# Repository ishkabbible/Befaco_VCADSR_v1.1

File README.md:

# Befaco_VCADSR_v1.1
Hamara Labs modified version of the Befaco version 1 VCADSR

The original files from Befaco are available here:
https://www.befaco.org/en/sinte-modular/en-produccion/vc-adsrv1/

Original design by Juergen Haible (http://www.jhaible.info/tonline_stuff/hj_vc_hadsr.html)

and Tom Gamble (http://synthdiy.fonitronik.de/files/4613/8287/9784/vcradsr.pdf)

I fixed a couple of bugs
  1) the inputs to the unused half of the 4013 were left floating - they are now properly grounded
  2) The trigger input to the used half of the 4013 was effectively floating whenever there was no gate input present, 
  due to the reverse biased D2. Added R26 to hold the trigger input at ground when D2 is reverse biased
  3) A retrigger bug was identified by someone somewhere, and photos of a haywire patch have been routinely distributed on line.
  That mod has been incorporated on the PCB as D6 and T8
  
I also updated the layout to use parts that are more readily available than the parts used in the original design. 
  
This repository contains 2 PCBs (FRONT and BACK) and one panel, all in KiCAD (http://kicad.org/)

The BOM is at https://docs.google.com/spreadsheets/d/1yNOWsHSHRAM60BiDUVynL0L72_J8PpAY8x3tWKFwJsM/edit?usp=sharing
This file takes precedence over the BOM in the assembly instructions document.

PCBs and panels *may* be available from Hamara Labs. Email HamaraLabs1 (at) gmail (dot) com to find out.

I believe all these files are correct, but I make no warranty whatsoever. Build at your own risk. If you find any problems with these files, please contact Hamara Labs at HamaraLabs1 (at) gmail (dot) com and I will update the files.

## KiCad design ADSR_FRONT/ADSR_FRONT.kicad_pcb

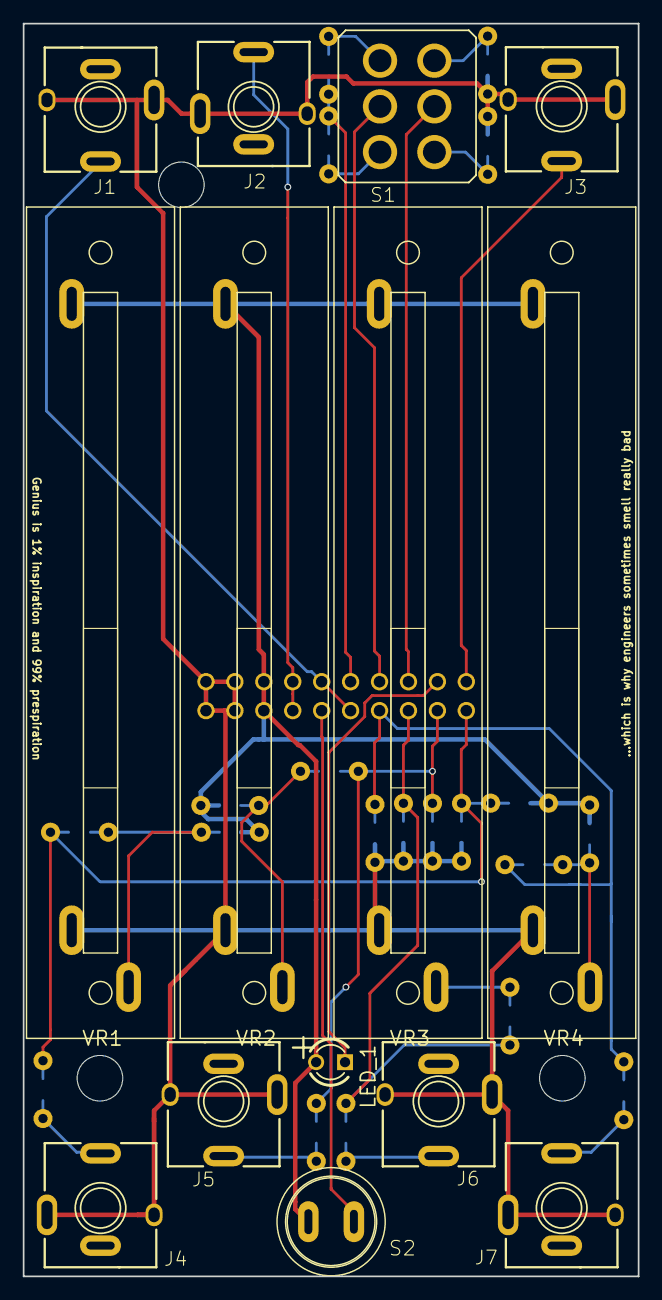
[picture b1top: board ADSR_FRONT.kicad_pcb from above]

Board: 2 copper layers, 54.0 x 110.0 mm, 38 parts (0 on the bottom side), 26 nets.

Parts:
@HOLE0, @HOLE1, @HOLE2: Keystone_8848_spacer
J1, J2, J3, J4, J5, J6, J7: PJ301BM; PJ301BM-JACK-slots
J8: MA10-2
LED_1: LED3MM; Befaco_LED3MM
R100, R101, R103, R107, R108, R109, R114, R115: 30K; Befaco-0204_5_SMD
R102, R110, R111: 10K; Befaco-0204_5_SMD
R104, R105, R106: 1K; Befaco-0204_5_SMD
R112: 68K; Befaco-0204_5_SMD
R113: 20K; Befaco-0204_5_SMD
R116: 27K; Befaco-0204_5_SMD
R117: 15K; Befaco-0204_5_SMD
R118: 270R; Befaco-0204_5_SMD
R119: 100K; Befaco-0204_5_SMD
S1: Toggle; Befaco_DPDT_toggle
S2: PS1024; Button_PS1024
VR1, VR2, VR3, VR4: 100K; Befaco_VCADSR_SLIDER

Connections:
+12V: J8.15, J8.16, LED_1.A, R102.2, R110.2, R111.2, R112.1, S2.P$1, VR1.P$3, VR2.P$3, VR3.P$3, VR4.P$3
/N$2: R114.1, VR3.P$2
/N$3: J6.3, R103.1
/N$11: R119.2, S1.4
/N$14: R118.2, S1.1
/N$18: R117.2, S1.3
/N$24: J4.3, R100.1
/N$27: R116.2, S1.6
/N$46: R108.1, R110.1, VR1.P$2
/N$48: R109.1, R111.1, VR4.P$2
/N$49: R102.1, R115.1, VR2.P$2
/N$50: J7.3, R101.1
/N$51: J5.3, R107.1
GND: J1.1, J1.4, J2.1, J2.4, J3.1, J3.4, J4.1, J4.4, J5.1, J5.4, J6.1, J6.4, J7.1, J7.4, J8.17, J8.18, J8.19, J8.20, R104.2, R105.2, R106.2, R113.2, R116.1, R119.1, VR1.P$1, VR2.P$1, VR3.P$1, VR4.P$1
TO_ATTACK_CV: J8.1, R100.2, R104.1, R108.2, R112.2
TO_DECCAY_CV: J8.3, R105.1, R107.2, R115.2
TO_GATE_IN: J1.3, J8.9, J8.12
TO_IC2_5: J8.10, R117.1, R118.1
TO_IC5_6: J8.8, S1.2
TO_IC_1_X: J8.6, S1.5
TO_LED: J8.4, LED_1.K
TO_MANUAL_TRIG: J8.11, S2.P$2
TO_OUT: J3.3, J8.2
TO_RELEASE_CV: J8.7, R101.2, R106.1, R109.2
TO_SUSTAIN_CV: J8.5, R103.2, R113.1, R114.2
TO_TRIGG_IN: J2.3, J8.13, J8.14

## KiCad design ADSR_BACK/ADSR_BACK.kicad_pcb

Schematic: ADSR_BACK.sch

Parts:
C1, C2, C5, C6, C7, C8, C9, C10, C12, C13, C14: 100nF; RCL_C050-025X075
C3, C4: 10uF; RCL_E2-4
C11: 100p; RCL_C050-025X075
C15: 330nF; RCL_C050-025X075
D1, D2, D3, D4, D6: 1n4148; DIODE_D-5
FB1, FB2: self; RCL_0204_5
IC1: UA555N; LINEAR_DIL08
IC2: 4013N; 40XX_DIL14
IC3: 4052N; 40XX_DIL16
IC4: TL074P; LINEAR_DIL14
IC5: TL072P; LINEAR_DIL08
P1: power; CON-ML_ML10
P2: CON-LSTB_MA10-2
R1, R2, R9, R13, R15, R19, R25, R26: 100k; RCL_0204_5
R3, R6, R12: 22k; RCL_0204_5
R4: 33k; RCL_0204_5
R5, R22: 10k; RCL_0204_5
R7: 47k; RCL_0204_5
R8: 300; RCL_0204_5
R10: 1k; RCL_0204_5
R11: 27k; RCL_0204_5
R14: 75K; RCL_0204_5
R16: 3k3; RCL_0204_5
R17: 6k2; RCL_0204_5
R18: 43k; RCL_0204_5
R20: 1M; RCL_0204_5
R21: 56k; RCL_0204_5
R23: 220K; RCL_0204_5
R24: 2M; RCL_0204_5
T1, T2, T3, T4, T7: 2n3904; TRANSISTOR-NEU-TO92_TO92-EBC
T5, T6, T8: 2N3906; TRANSISTOR-NEU-TO92_TO92-EBC

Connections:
+12V: C1.2, C2.2, C4.+, C7.2, C8.2, C13.2, C14.2, FB1.1, IC1.4 (R), IC1.8 (V+), IC2.14 (VDD), IC3.15 (X2), IC3.16 (VCC), IC4.4 (V+), IC5.8 (V+), P2.15, P2.16, R3.1, R5.1, R6.1, R21.2
-12V: C3.-, C6.1, C9.1, C12.1, FB2.1, IC4.11 (V-), IC5.4 (V-)
/ATTACK_CV: P2.2, R12.1
/DECCAY_CV: IC3.1 (Y0), P2.4
/GATE_IN: D3.A, P2.10
/IC5_6: IC4.6 (-IN), P2.7, R7.1
/IC25: C15.2, IC4.3 (+IN), IC4.14 (OUT), IC5.5 (+IN), P2.9, T8.E
/IC_1_X: IC3.13 (X), IC4.5 (+IN), P2.5
/LED: P2.3, T3.C
/MANUAL_TRIG: D4.C, P2.11, P2.12, R15.1
/N$4: C10.2, IC3.10 (A), R6.2, T1.C
/N$5: D1.C, D3.C, R2.1
/N$6: R1.2, R2.2, T1.B
/N$7: C5.1, IC1.5 (CV)
/N$8: FB1.2, P1.9, P1.10
/N$10: R16.2, T4.E, T5.E, T6.E, T7.E
/N$12: C15.1, IC4.13 (-IN), T6.C, T7.C, T8.C
/N$13: IC4.7 (OUT), R7.2, R17.1
/N$15: R4.1, T2.B
/N$16: R14.2, R23.2, T6.B
/N$17: R12.2, T4.B
/N$19: IC3.3 (Y), R14.1
/N$21: IC1.6 (THR), IC4.1 (OUT), R19.1
/N$22: C11.1, IC4.9 (-IN), R17.2, T4.C, T5.C
/N$23: C11.2, IC4.8 (OUT), R16.1
/N$28: IC4.2 (-IN), R19.2, R25.2
/N$29: IC5.6 (-IN), R11.1, R18.2
/N$30: IC5.7 (OUT), R10.2, R13.1, R18.1
/N$33: FB2.2, P1.1, P1.2
/N$34: IC5.3 (+IN), R15.2, R20.2
/N$35: D1.A, IC2.1 (Q)
/N$36: IC1.3 (Q), IC3.9 (B), R4.2
/N$38: IC2.4 (R), R3.2, T2.C
/N$39: IC5.2 (-IN), R21.1, R22.2, R24.2
/N$41: D2.C, IC2.6 (S), R26.2
/N$42: D2.A, IC5.1 (OUT), R24.1
/N$78: R8.1, T3.E
/N$79: R9.1, R13.2, T3.B
/OUT: P2.1, R10.1
/RELEASE_CV: IC3.4 (Y3), IC3.5 (Y1), P2.8
/SUSTAIN_CV: IC3.12 (X0), P2.6
/TRIGG_IN: D4.A, P2.13, P2.14
GND: C1.1, C2.1, C3.+, C4.-, C5.2, C6.2, C7.1, C8.1, C9.2, C12.2, C13.1, C14.1, IC1.1 (GND), IC2.3 (CLK), IC2.5 (D), IC2.7 (VSS), IC2.8 (S), IC2.9 (D), IC2.10 (R), IC2.11 (CLK), IC3.2 (Y2), IC3.6 (INH), IC3.7 (VEE), IC3.8 (GND), IC3.11 (X3), IC3.14 (X1), IC4.10 (+IN), IC4.12 (+IN), P1.3, P1.4, P1.5, P1.6, P1.7, P1.8, P2.17, P2.18, P2.19, P2.20, R1.1, R8.2, R9.2, R11.2, R20.1, R22.1, R23.1, R25.1, R26.1, T1.E, T2.E, T5.B, T7.B
unnamed: D6.A, T8.B
retrig: C10.1, D6.C, IC1.2 (TR), R5.2

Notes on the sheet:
Decay/sustain
Release
Attack

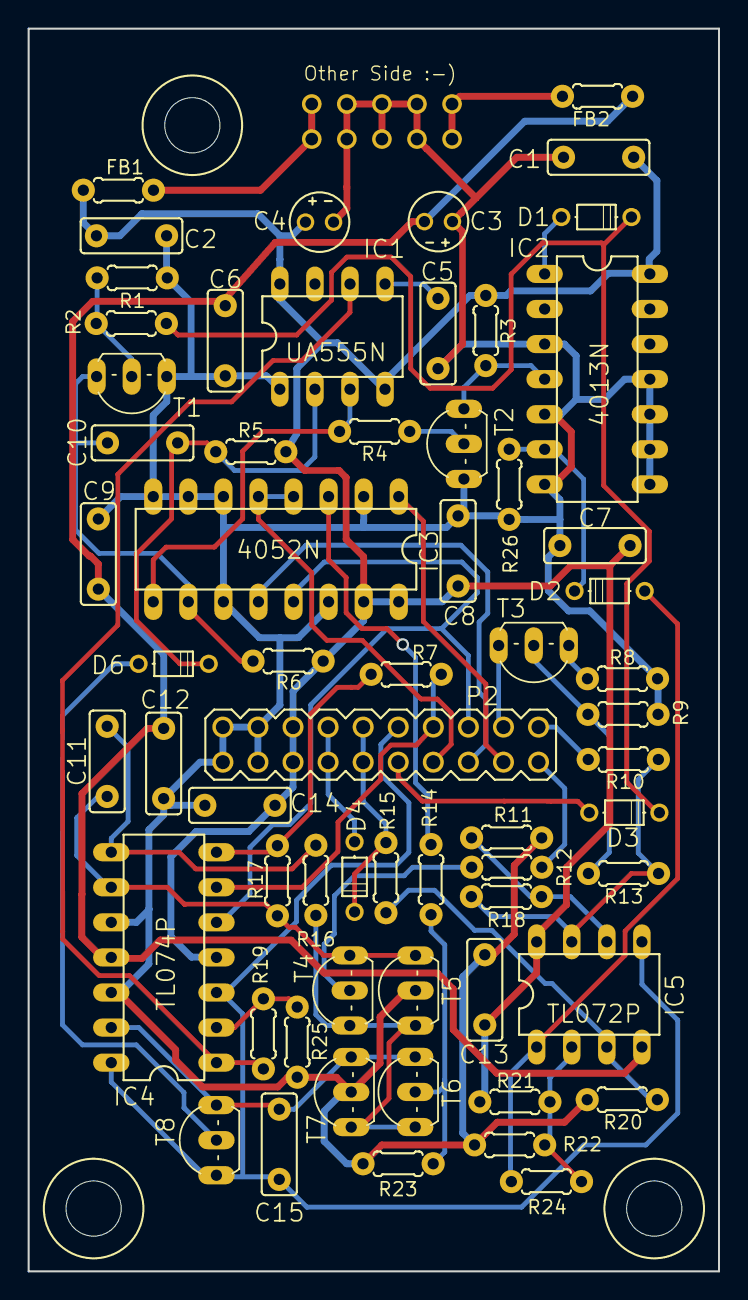
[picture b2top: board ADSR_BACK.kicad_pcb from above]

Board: 2 copper layers, 50.0 x 90.0 mm, 66 parts (0 on the bottom side), 45 nets.

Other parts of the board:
@HOLE0, @HOLE1, @HOLE2: Keystone_8848_spacer

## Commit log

2017-12-16 First commit of ADSR_BACK
2017-12-16 Uploading full local repository
2017-12-16 Add link to BOM, links to original sources, warranty disclaimer
2017-12-16 Uploading a few stragglers
2017-12-16 Add link to BOM, links to original design sources, and warranty disclaimer
2017-12-16 Add link to BOM, links to original design sources, warranty disclaimer.
2021-11-07 Update link
    https://forum.kicad.info/t/warning-avoid-all-links-to-kicad-pcb-org-use-kicad-org/31521/

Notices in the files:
ADSR_BACK/ADSR_BACK.kicad_pcb:
Public domain PCB
